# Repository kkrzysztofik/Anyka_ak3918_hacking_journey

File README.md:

# Anyka AK3918 Hacking Journey

Reverse engineering and hacking journey for Chinese IP cameras based on Anyka AK3918 SoC

## Credits

This project was originally developed by **Gerge** (<https://gitea.raspiweb.com/Gerge/Anyka_ak3918_hacking_journey>) and has been continued with additional improvements and fixes. The original work involved extensive reverse engineering of the Anyka AK3918 platform and development of custom firmware and applications.

## Recent Updates

- **ONVIF Rust Rewrite**: Complete rewrite of ONVIF services in Rust for memory safety and modern async architecture
- **ONVIF 24.12 Compliance**: Targeting latest ONVIF specifications with Profile S/T support
- **Modern Stack**: Built on `tokio` and `axum` for high-performance asynchronous I/O
- **Comprehensive Testing**: Unit tests with `mockall` and integration test framework
- **Code Quality**: Rust's ownership model prevents common embedded pitfalls
- **Web Interface**: ONVIF and legacy interfaces with clear separation

## Quick Start

### ONVIF Rust Implementation

```bash
cd cross-compile/onvif-rust

# Use the custom toolchain's cargo
export CARGO=/home/kmk/anyka-dev/toolchain/arm-anykav200-crosstool-ng/bin/cargo

# Build for host (testing)
$CARGO build
$CARGO test

# Build for target (Anyka AK3918)
$CARGO build --release --target armv5te-unknown-linux-uclibceabi
```

> **⚠️ CRITICAL**: Always use the custom toolchain's cargo binary for target builds.

## Security Warnings

> [!CAUTION]
> **TLS Required for Production**
>
> ONVIF 24.12 uses WS-Security with SHA-1/MD5 digest authentication (weak by modern standards). **Never use authentication without TLS in production** - credentials can be intercepted and cracked over unencrypted HTTP. See the [TLS Setup Guide](https://github.com/kkrzysztofik/Anyka_ak3918_hacking_journey/wiki/TLS-Setup) in the wiki for configuration instructions.

## Documentation

**📚 For comprehensive documentation, please visit the [GitHub Wiki](https://github.com/kkrzysztofik/Anyka_ak3918_hacking_journey/wiki).**

The wiki contains detailed information on:

- **Home** - Project overview and navigation
- **ONVIF Rust Implementation** - Complete ONVIF 24.12 implementation details
- **Development Environment** - Toolchain setup and build instructions
- **Web Interface** - Web UI documentation
- **Development Guide** - Development workflow and best practices
- **Troubleshooting** - Common issues and solutions
- **Static Analysis Tools** - Code quality and security analysis
- **Legacy Applications** - Legacy tools and applications
- **Resources** - External links and quick start guides
- **Future Enhancements** - Planned features and roadmap

## Key Features

- **ONVIF Rust Implementation** - Modern, memory-safe ONVIF 24.12 server
- **Memory Safety** - Rust's ownership model prevents buffer overflows and use-after-free errors
- **Asynchronous Architecture** - High-performance async I/O using `tokio` and `axum`
- **Comprehensive Testing** - Unit tests with `mockall` and integration test framework
- **Web Interfaces** - Both ONVIF and legacy interfaces with clear separation

## Status

- **Current Status**: Active Development (Alpha)
- **Target Platform**: Anyka AK3918 (ARM926EJ-S, 32MB RAM)
- **ONVIF Compliance**: Profile S/T (Targeting v24.12)

> **⚠️ Current Limitation**: The ONVIF Rust implementation currently uses **stub implementations** for the Platform Abstraction Layer. Real Anyka hardware integration is not yet implemented. All ONVIF API calls are handled by stub/mock implementations for testing and development purposes.

## Quick Reference

The ONVIF server implements:

- **Device Service**: System information, network configuration, user management
- **Media Service**: Video profiles, RTSP stream URI generation, encoder configuration
- **PTZ Service**: Pan/Tilt/Zoom control with preset management
- **Imaging Service**: Image parameter adjustment (brightness, contrast, saturation, sharpness)

---

**For detailed documentation, setup instructions, troubleshooting, and development guides, please see the [GitHub Wiki](https://github.com/kkrzysztofik/Anyka_ak3918_hacking_journey/wiki).**

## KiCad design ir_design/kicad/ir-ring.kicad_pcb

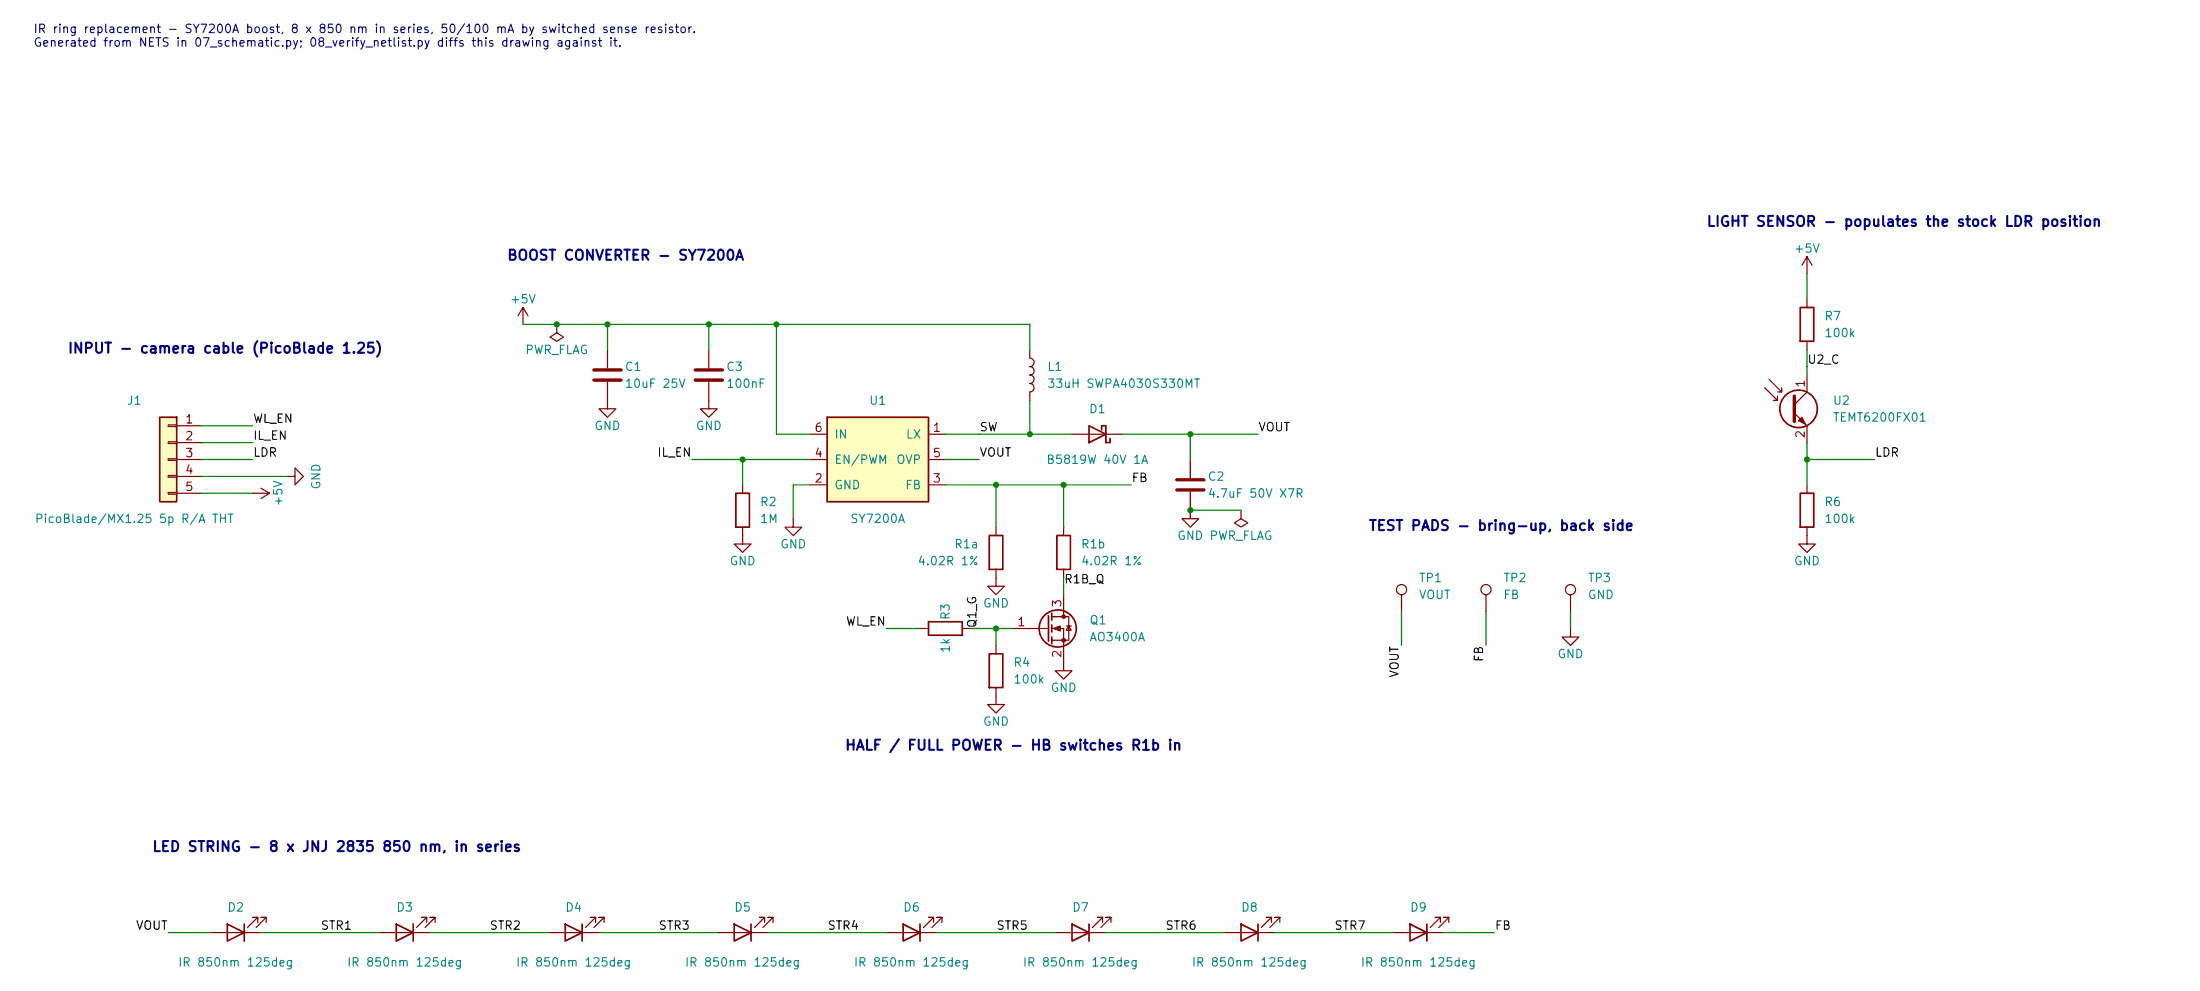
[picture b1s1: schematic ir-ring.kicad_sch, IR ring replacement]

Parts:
C1: 10uF 25V; C_0805_2012Metric; MPN CL21A106KAYNNNE; LCSC C15850
C2: 4.7uF 50V X7R; C_1206_3216Metric; MPN 1206B475K500NT; LCSC C29823
C3: 100nF; C_0805_2012Metric; MPN CC0805KRX7R9BB104; LCSC C49678
D1: B5819W 40V 1A; D_SOD-123; MPN B5819W SL; LCSC C8598
D2, D3, D4, D5, D6, D7, D8, D9: IR 850nm 125deg; LED_2835_JNJ_CW; MPN JNJ-L-2835CW-85020D-S-Q2; LCSC C22447924
J1: PicoBlade/MX1.25 5p R/A THT; Molex_PicoBlade_53048-0510_1x05_P1.25mm_Horizontal_Ring0.275; MPN 530480510; LCSC C588276
L1: 33uH SWPA4030S330MT; L_Sunlord_SWPA4030S; MPN SWPA4030S330MT; LCSC C83470
Q1: AO3400A; SOT-23; MPN AO3400A; LCSC C20917
R1a, R1b: 4.02R 1%; R_0805_2012Metric; MPN WR08W4R02FTL; LCSC C367870
R2: 1M; R_0805_2012Metric; MPN 0805W8F1004T5E; LCSC C17514
R3: 1k; R_0805_2012Metric; MPN 0805W8F1001T5E; LCSC C17513
R4, R6, R7: 100k; R_0805_2012Metric; MPN 0805W8F1003T5E; LCSC C149504
TP1: VOUT; TestPoint_Pad_D1.5mm
TP2: FB; TestPoint_Pad_D1.5mm
TP3: GND; TestPoint_Pad_D1.5mm
U1: SY7200A; SOT-23-6; MPN SY7200AABC; LCSC C107309
U2: TEMT6200FX01; TEMT6200_0805; MPN TEMT6200FX01; LCSC C143695

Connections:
+5V: C1.1, C3.1, J1.5, L1.1, R7.1, U1.6 (IN)
/FB: D9.1 (K), R1a.1, R1b.1, TP2.1, U1.3 (FB)
/IL_EN: J1.2, R2.1, U1.4 (EN/PWM)
/LDR: J1.3, R6.1, U2.2 (E)
/Q1_G: Q1.1 (G), R3.2, R4.1
/R1B_Q: Q1.3 (D), R1b.2
/STR1: D2.1 (K), D3.2 (A)
/STR2: D3.1 (K), D4.2 (A)
/STR3: D4.1 (K), D5.2 (A)
/STR4: D5.1 (K), D6.2 (A)
/STR5: D6.1 (K), D7.2 (A)
/STR6: D7.1 (K), D8.2 (A)
/STR7: D8.1 (K), D9.2 (A)
/SW: D1.2 (A), L1.2, U1.1 (LX)
/U2_C: R7.2, U2.1 (C)
/VOUT: C2.1, D1.1 (K), D2.2 (A), TP1.1, U1.5 (OVP)
/WL_EN: J1.1, R3.1
GND: C1.2, C2.2, C3.2, J1.4, Q1.2 (S), R1a.2, R2.2, R4.2, R6.2, TP3.1, U1.2 (GND)

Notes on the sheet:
IR ring replacement - SY7200A boost, 8 x 850 nm in series, 50/100 mA by switched sense resistor. Generated from NETS in 07_schematic.py; 08_verify_netlist.py diffs this drawing against it.
INPUT - camera cable (PicoBlade 1.25)
BOOST CONVERTER - SY7200A
HALF / FULL POWER - HB switches R1b in
LIGHT SENSOR - populates the stock LDR position
LED STRING - 8 x JNJ 2835 850 nm, in series
TEST PADS - bring-up, back side

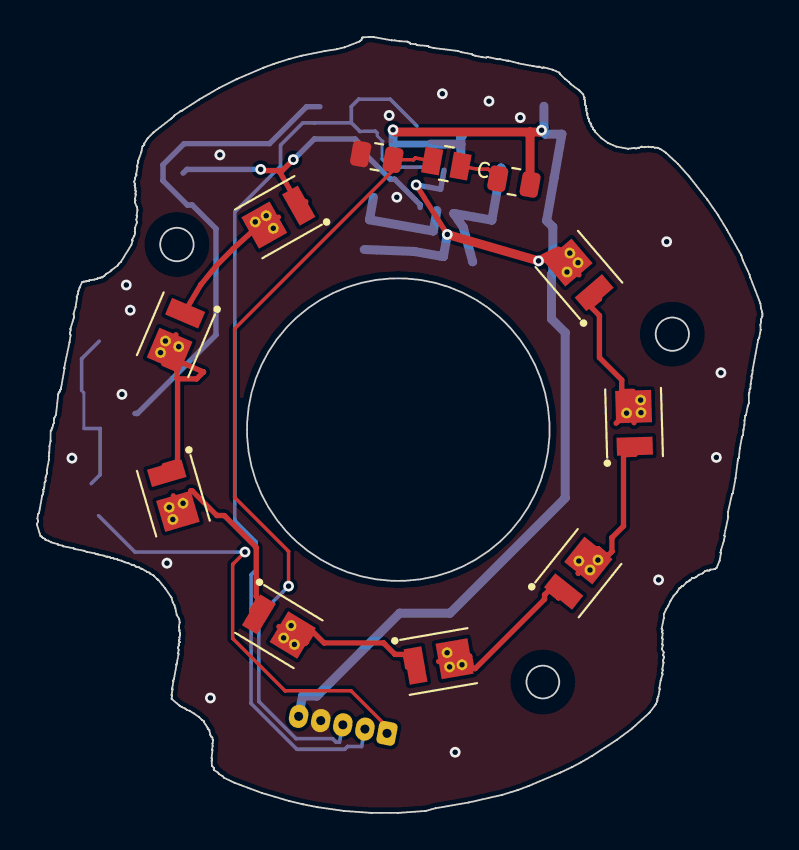
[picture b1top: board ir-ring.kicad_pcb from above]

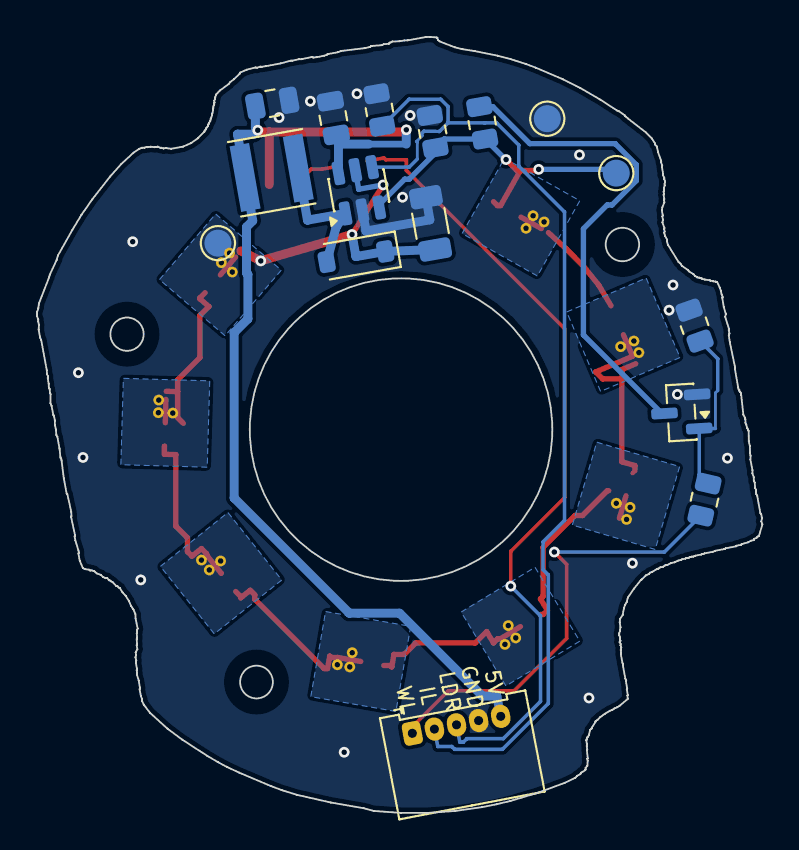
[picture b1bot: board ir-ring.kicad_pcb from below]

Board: 2 copper layers, 40.3 x 43.1 mm, 27 parts (16 on the bottom side), 18 nets.

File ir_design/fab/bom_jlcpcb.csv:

Comment,Designator,Footprint,LCSC Part #,Quantity,Manufacturer,Manufacturer Part #,Description
10uF 25V,C1,C_0805_2012Metric,C15850,1,Samsung Electro-Mechanics,CL21A106KAYNNNE,CAP CER 10uF 25V X5R 0805
4.7uF 50V X7R,C2,C_1206_3216Metric,C29823,1,FH,1206B475K500NT,CAP CER 4.7uF 50V X7R 1206
100nF,C3,C_0805_2012Metric,C49678,1,YAGEO,CC0805KRX7R9BB104,CAP CER 100nF 50V X7R 0805
B5819W 40V 1A,D1,D_SOD-123,C8598,1,JSCJ,B5819W SL,DIODE SCHOTTKY 40V SOD-123
IR 850nm 120deg,"D2,D3,D4,D5,D6,D7,D8,D9",LED_3535_JNJ_EW120,C22447930,8,JNJOPTO,JNJ-L-3535EW120-85035D-SL-J2,EMITTER IR 850nm 1000mA SMD3535
PicoBlade/MX1.25 5p R/A THT,J1,Molex_PicoBlade_53048-0510_1x05_P1.25mm_Horizontal_Ring0.275,C588276,1,MOLEX,530480510,CONN HEADER TH R/A 5POS 1.25mm
33uH SWPA4030S330MT,L1,L_Sunlord_SWPA4030S,C83470,1,Sunlord,SWPA4030S330MT,Power inductor 33uH 20% 1.1A 429mOhm 4x4mm
AO3400A,Q1,SOT-23,C20917,1,AOS,AO3400A,MOSFET N-CH 30V SOT-23
4.02R 1%,"R1a,R1b",R_0805_2012Metric,C367870,2,Walsin,WR08W4R02FTL,RES 4.02 Ohm 1% 125mW 0805
1M,R2,R_0805_2012Metric,C17514,1,UNI-ROYAL,0805W8F1004T5E,RES 1M 1% 125mW 0805
1k,R3,R_0805_2012Metric,C17513,1,UNI-ROYAL,0805W8F1001T5E,RES 1k 1% 125mW 0805
100k,"R4,R6,R7",R_0805_2012Metric,C149504,3,UNI-ROYAL,0805W8F1003T5E,RES 100k 1% 125mW 0805
SY7200A,U1,SOT-23-6,C107309,1,Silergy,SY7200AABC,30V High Current Boost LED Driver
TEMT6200FX01,U2,TEMT6200_0805,C143695,1,VISHAY,TEMT6200FX01,Ambient Light Sensor in 0805 Package
